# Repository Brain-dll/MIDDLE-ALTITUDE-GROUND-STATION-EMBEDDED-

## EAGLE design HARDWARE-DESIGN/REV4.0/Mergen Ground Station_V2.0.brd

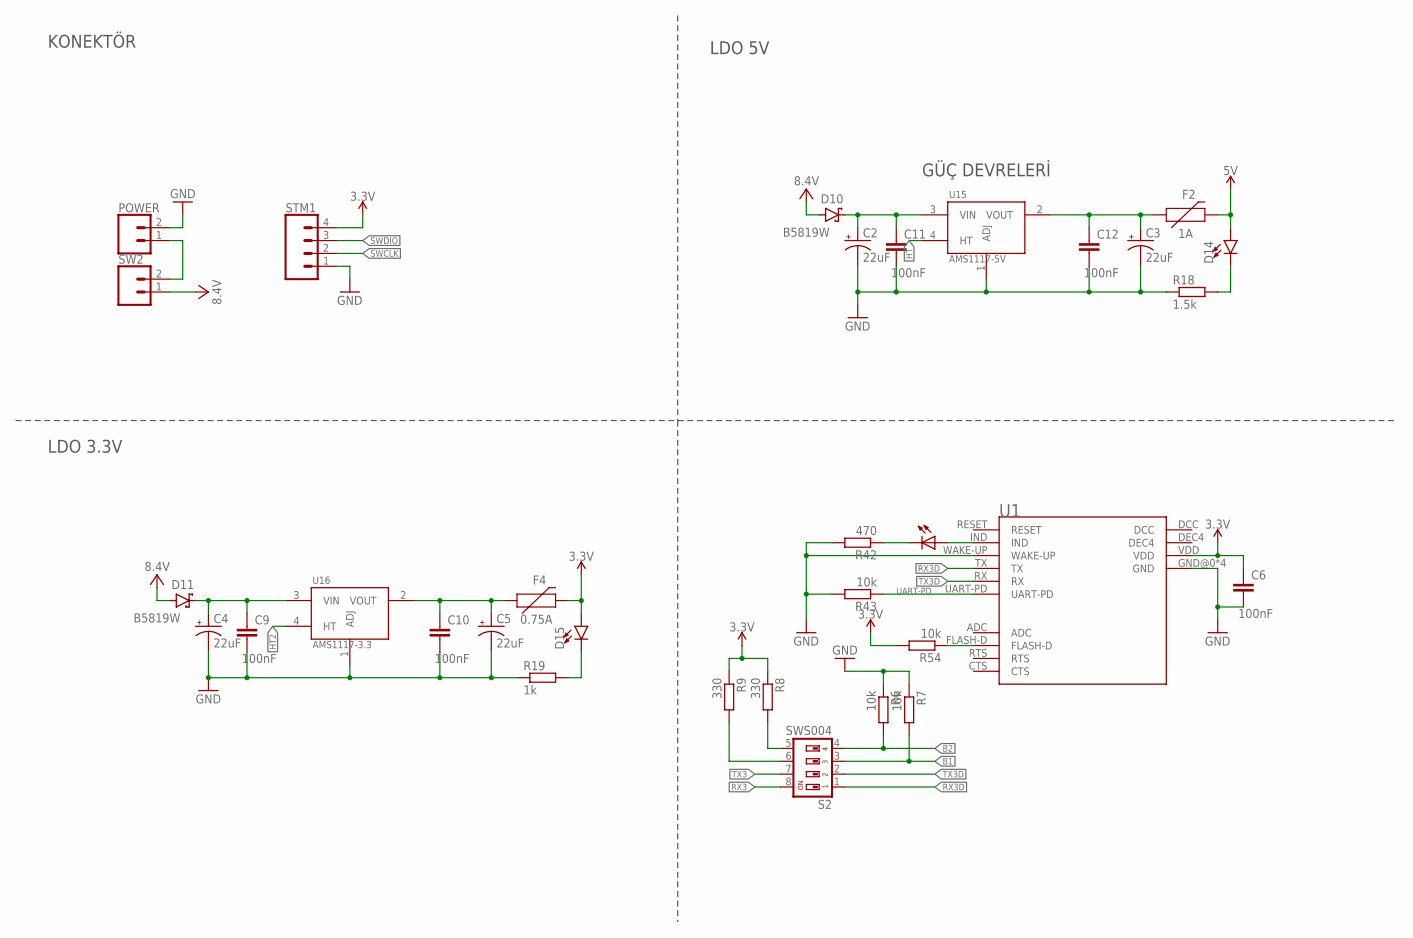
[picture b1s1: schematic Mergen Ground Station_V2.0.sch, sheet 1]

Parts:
C2, C3, C4, C5: 22uF; CT3528
C6, C9, C10, C11, C12: 100nF; C0603
D10, D11: B5819W; SODFL3718X115
D14, D15: LED0603; LED-0603
DRM3: kirmizi; CHIP-LED0805
F2: 1A; 1206
F4: 0.75A; 1206
POWER: CONN_023.5MM-NO_SILK; SCREWTERMINAL-3.5MM-2-NS
R6, R7, R43, R54: 10k; R0603
R8, R9: 330; R0603
R18: 1.5k; R0603
R19: 1k; R0603
R42: 470; R0603
S2: SWS004; SMS-004
STM1: CONN_04; 1X04
SW2: CONN_023.5MM-NO_SILK; SCREWTERMINAL-3.5MM-2-NS
U1: MDBT42T-AT
U15: AMS1117-5V; SOT229P700X180-4N
U16: AMS1117-3.3; SOT229P700X180-4N

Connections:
3.3V: C6.1, D15.A, F4.2, R8.1, R9.1, R54.2, STM1.4, U1.VDD; also elsewhere on the board
5V: D14.A, F2.2; also elsewhere on the board
B1: R7.2, S2.3; also elsewhere on the board
B2: R6.2, S2.4; also elsewhere on the board
FLASH-D: R54.1, U1.FLASH-D; also elsewhere on the board
GND: C2.-, C3.-, C4.-, C5.-, C6.2, C9.2, C10.2, C11.2, C12.2, POWER.2, R6.1, R7.1, R18.1, R19.1, R42.2, R43.2, STM1.1, U1.GND@0 (GND), U1.GND@1 (GND), U1.GND@2 (GND), U1.GND@3 (GND), U1.WAKE-UP, U15.1 (ADJ), U16.1 (ADJ); also elsewhere on the board
HT: U15.4 (HT)
HT2: U16.4 (HT)
unnamed: DRM3.A, U1.IND
unnamed: DRM3.C, R42.1
unnamed: R9.2, S2.6
unnamed: R8.2, S2.5
unnamed: C2.+, C11.1, D10.1 (C), U15.3 (VIN)
unnamed: C3.+, C12.1, F2.1, U15.2 (VOUT)
unnamed: C4.+, C9.1, D11.1 (C), U16.3 (VIN)
unnamed: C5.+, C10.1, F4.1, U16.2 (VOUT)
unnamed: POWER.1, SW2.2
unnamed: D14.C, R18.2
unnamed: D15.C, R19.2
RX3: S2.8; also elsewhere on the board
RX3D: S2.1, U1.TX
SWCLK: STM1.2; also elsewhere on the board
SWDIO: STM1.3; also elsewhere on the board
TX3: S2.7; also elsewhere on the board
TX3D: S2.2, U1.RX
UART-PD: R43.1, U1.UART-PD; also elsewhere on the board
VCC: D10.2 (A), D11.2 (A), SW2.1; also elsewhere on the board

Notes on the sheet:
GÜÇ DEVRELERİ
KONEKTÖR
LDO 5V
LDO 3.3V

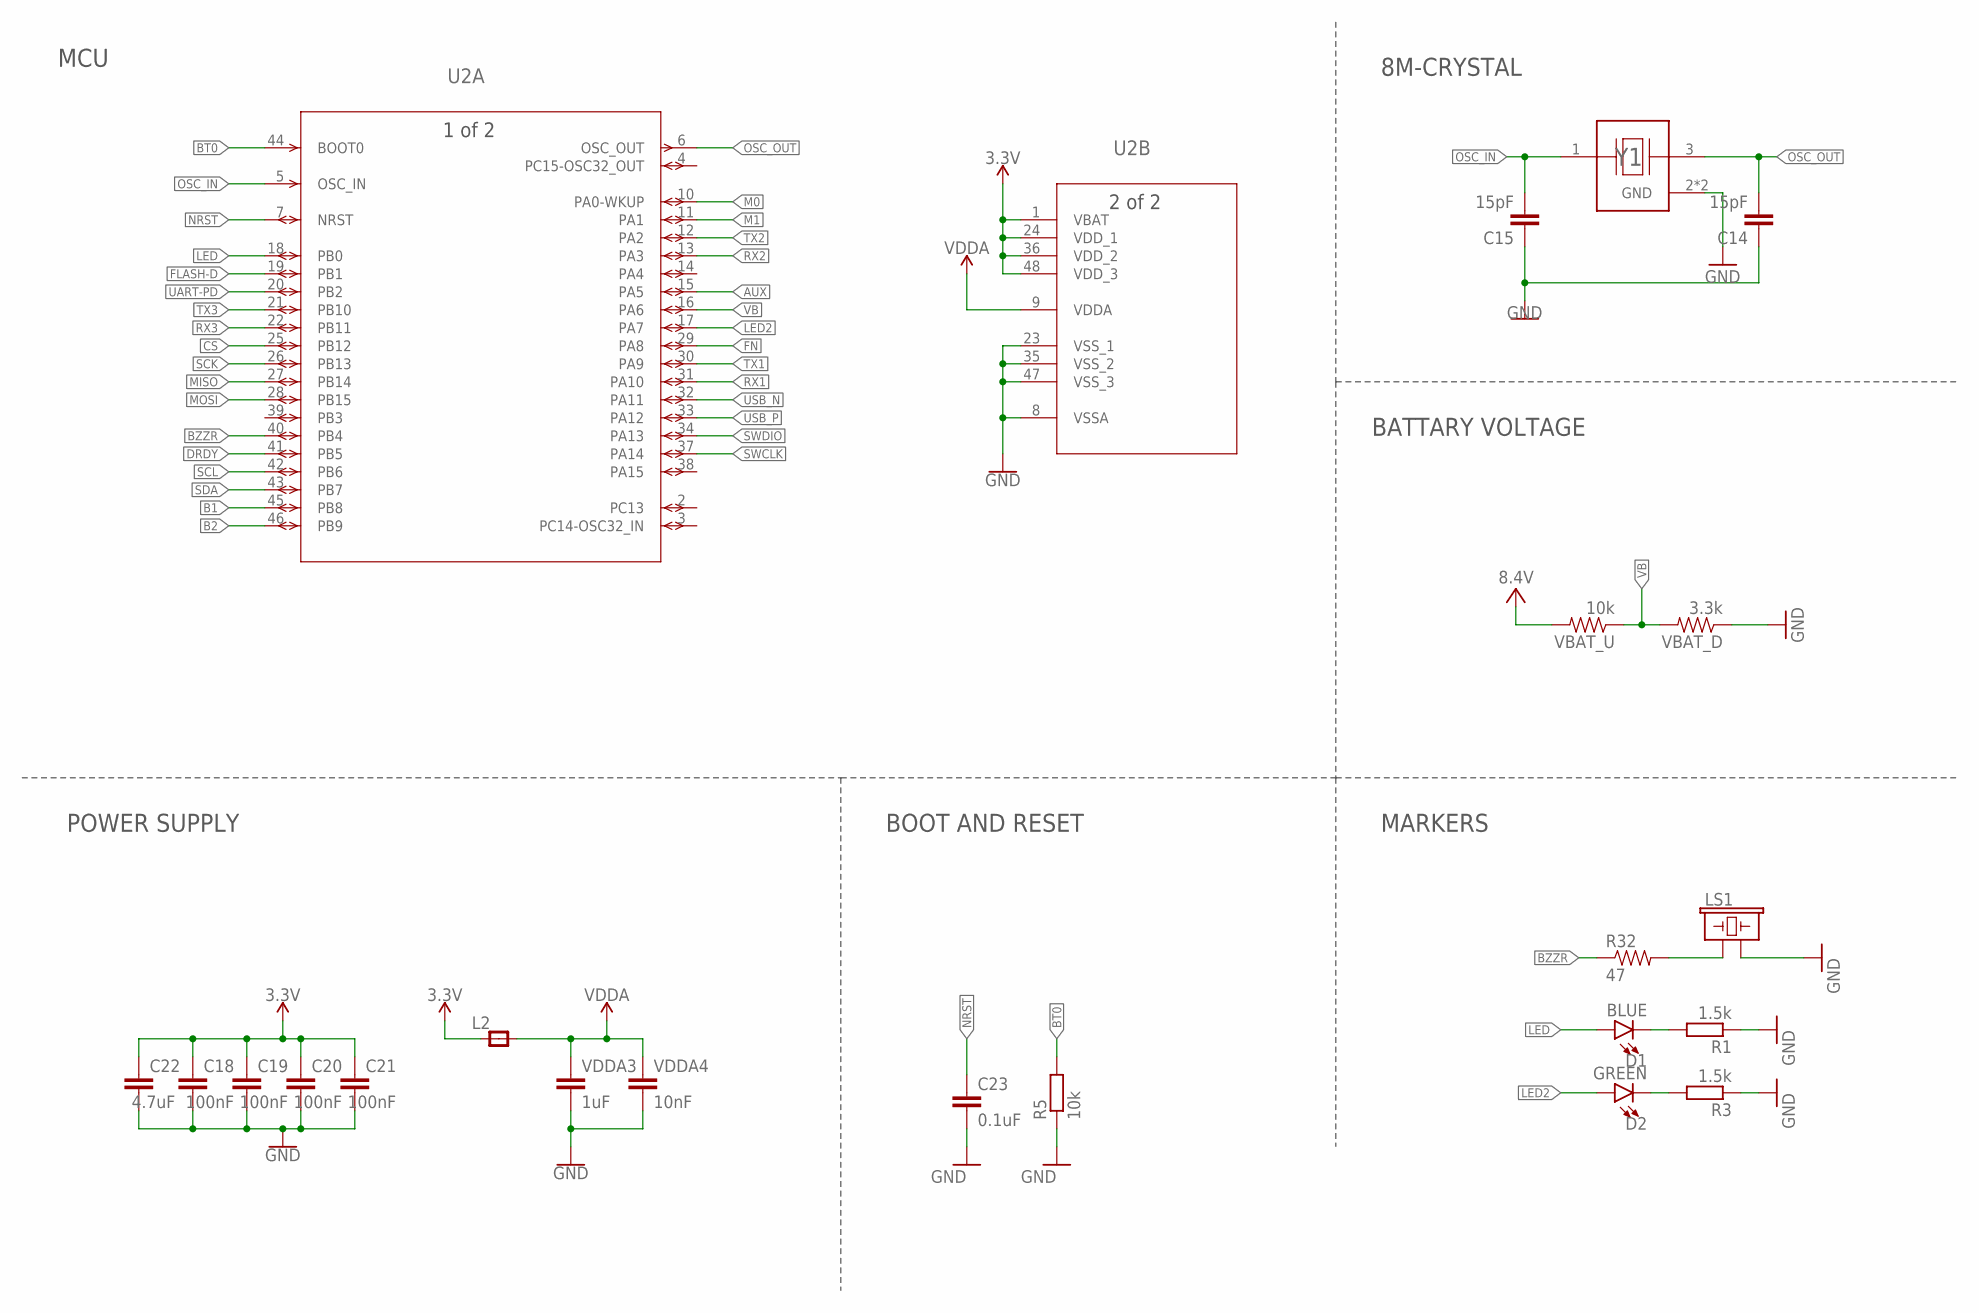
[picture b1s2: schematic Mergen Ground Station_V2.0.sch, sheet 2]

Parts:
C14, C15: 15pF; C0603
C18, C19, C20, C21: 100nF; C0603
C22: 4.7uF; C0603
C23: 0.1uF; C0603
D1: BLUE; LED-0603
D2: GREEN; LED-0603
L2: RC-MASTER-SMD_FB_0805MP; RC-MASTER-SMD_L0805MP
LS1: BUZZER-PTH; BUZZER-12MM
R1, R3: 1.5k; R0603
R5: 10k; R0603
R32: 47; 0603
U2: STM32F103C8T6; LQFP48-7X7MM
VBAT_D: 3.3k; 0603-RES
VBAT_U: 10k; 0603-RES
VDDA3: 1uF; 0603
VDDA4: 10nF; 0603
Y1: ABMM2-8.000MHZ-E2-T; XTAL_ABMM2-8.000MHZ-E2-T

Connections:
3.3V: C18.1, C19.1, C20.1, C21.1, C22.1, L2.1, U2.1 (VBAT), U2.24 (VDD_1), U2.36 (VDD_2), U2.48 (VDD_3); also elsewhere on the board
AUX: U2.15 (PA5); also elsewhere on the board
B1: U2.45 (PB8); also elsewhere on the board
B2: U2.46 (PB9); also elsewhere on the board
BT0: R5.2, U2.44 (BOOT0)
BZZR: R32.1, U2.40 (PB4)
CS: U2.25 (PB12); also elsewhere on the board
DRDY: U2.41 (PB5); also elsewhere on the board
FLASH-D: U2.19 (PB1); also elsewhere on the board
FN: U2.29 (PA8); also elsewhere on the board
GND: C14.1, C15.1, C18.2, C19.2, C20.2, C21.2, C22.2, C23.2, LS1.- (2), R1.1, R3.1, R5.1, U2.8 (VSSA), U2.23 (VSS_1), U2.35 (VSS_2), U2.47 (VSS_3), VBAT_D.1, VDDA3.2, VDDA4.2, Y1.2 (GND), Y1.4 (GND); also elsewhere on the board
LED: D1.A, U2.18 (PB0)
LED2: D2.A, U2.17 (PA7)
M0: U2.10 (PA0-WKUP); also elsewhere on the board
M1: U2.11 (PA1); also elsewhere on the board
MISO: U2.27 (PB14); also elsewhere on the board
MOSI: U2.28 (PB15); also elsewhere on the board
unnamed: D1.C, R1.2
unnamed: D2.C, R3.2
unnamed: LS1.+ (1), R32.2
NRST: C23.1, U2.7 (NRST)
OSC_IN: C15.2, U2.5 (OSC_IN), Y1.1
OSC_OUT: C14.2, U2.6 (OSC_OUT), Y1.3
RX1: U2.31 (PA10); also elsewhere on the board
RX2: U2.13 (PA3); also elsewhere on the board
RX3: U2.22 (PB11); also elsewhere on the board
SCK: U2.26 (PB13); also elsewhere on the board
SCL: U2.42 (PB6); also elsewhere on the board
SDA: U2.43 (PB7); also elsewhere on the board
SWCLK: U2.37 (PA14); also elsewhere on the board
SWDIO: U2.34 (PA13); also elsewhere on the board
TX1: U2.30 (PA9); also elsewhere on the board
TX2: U2.12 (PA2); also elsewhere on the board
TX3: U2.21 (PB10); also elsewhere on the board
UART-PD: U2.20 (PB2); also elsewhere on the board
USB_N: U2.32 (PA11); also elsewhere on the board
USB_P: U2.33 (PA12); also elsewhere on the board
VB: U2.16 (PA6), VBAT_D.2, VBAT_U.1
VCC: VBAT_U.2; also elsewhere on the board
VDDA: L2.2, U2.9 (VDDA), VDDA3.1, VDDA4.1

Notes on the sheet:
MCU
8M-CRYSTAL
BATTARY VOLTAGE
MARKERS
BOOT AND RESET
POWER SUPPLY

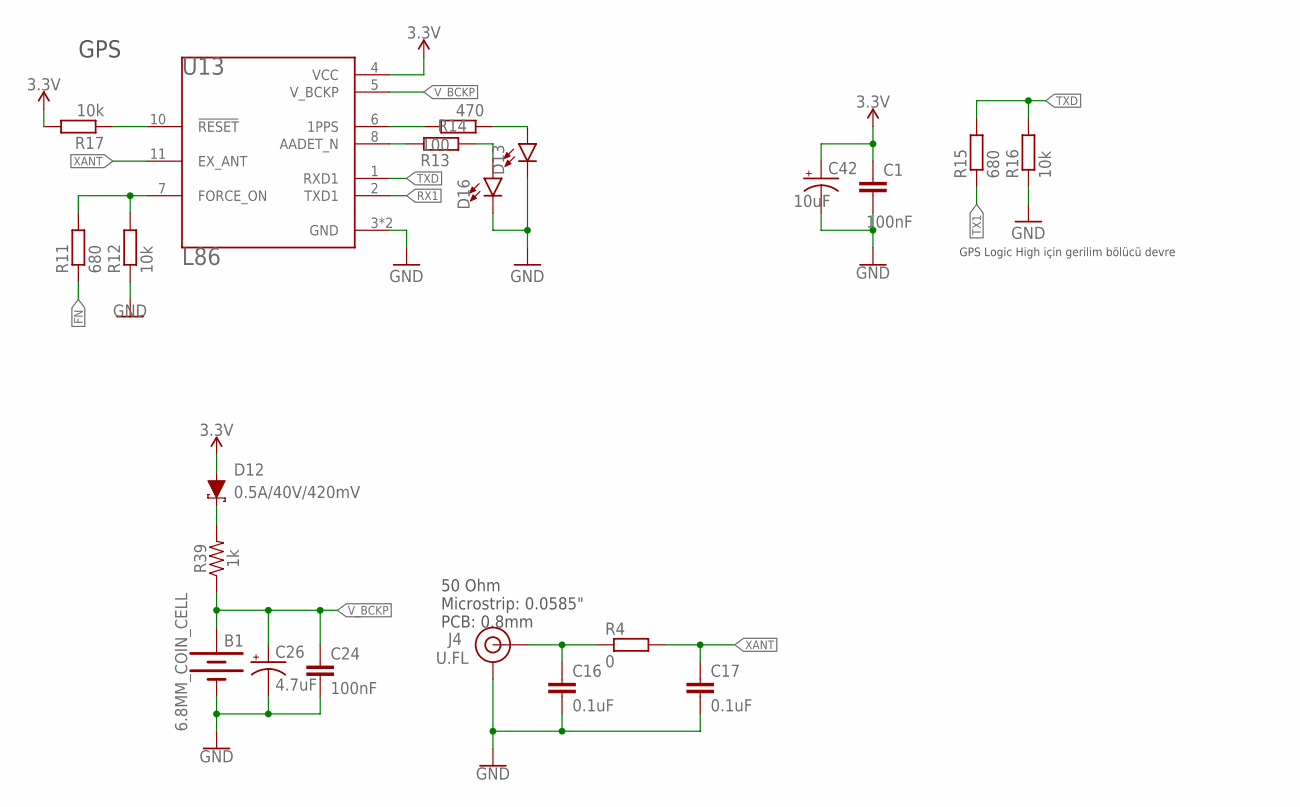
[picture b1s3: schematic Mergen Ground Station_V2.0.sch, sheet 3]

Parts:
B1: 6.8MM_COIN_CELL; BATTCON-6.8MM
C1, C24: 100nF; C0603
C16, C17: 0.1uF; C0603
C26: 4.7uF; A/3216-18R
C42: 10uF; EIA3216
D12: 0.5A/40V/420mV; SOD-323
D13, D16: LED0603; LED-0603
J4: U.FL
R4: 0; R0603
R11, R15: 680; R0603
R12, R16, R17: 10k; R0603
R13: 100; R0603
R14: 470; R0603
R39: 1k; 0603
U13: L86; XCVR_L86

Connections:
3.3V: C1.1, C42.+, D12.A, R17.2, U13.4 (VCC); also elsewhere on the board
FN: R11.1; also elsewhere on the board
GND: B1.-, C1.2, C16.2, C17.2, C24.2, C26.-, C42.-, D13.C, D16.C, J4.1 (GND), J4.2 (GND), R12.1, R16.1, U13.3 (GND), U13.12 (GND); also elsewhere on the board
unnamed: D16.A, R13.1
unnamed: D12.C, R39.2
unnamed: R17.1, U13.10 (!RESET)
unnamed: R14.2, U13.6 (1PPS)
unnamed: D13.A, R14.1
unnamed: R13.2, U13.8 (AADET_N)
unnamed: C16.1, J4.FEED (SIGNAL), R4.1
unnamed: R11.2, R12.2, U13.7 (FORCE_ON)
RX1: U13.2 (TXD1); also elsewhere on the board
TX1: R15.1; also elsewhere on the board
TXD: R15.2, R16.2, U13.1 (RXD1)
V_BCKP: B1.+, C24.1, C26.+, R39.1, U13.5 (V_BCKP)
XANT: C17.1, R4.2, U13.11 (EX_ANT)

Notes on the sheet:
GPS
GPS Logic High için gerilim bölücü devre
50 Ohm Microstrip: 0.0585" PCB: 0.8mm

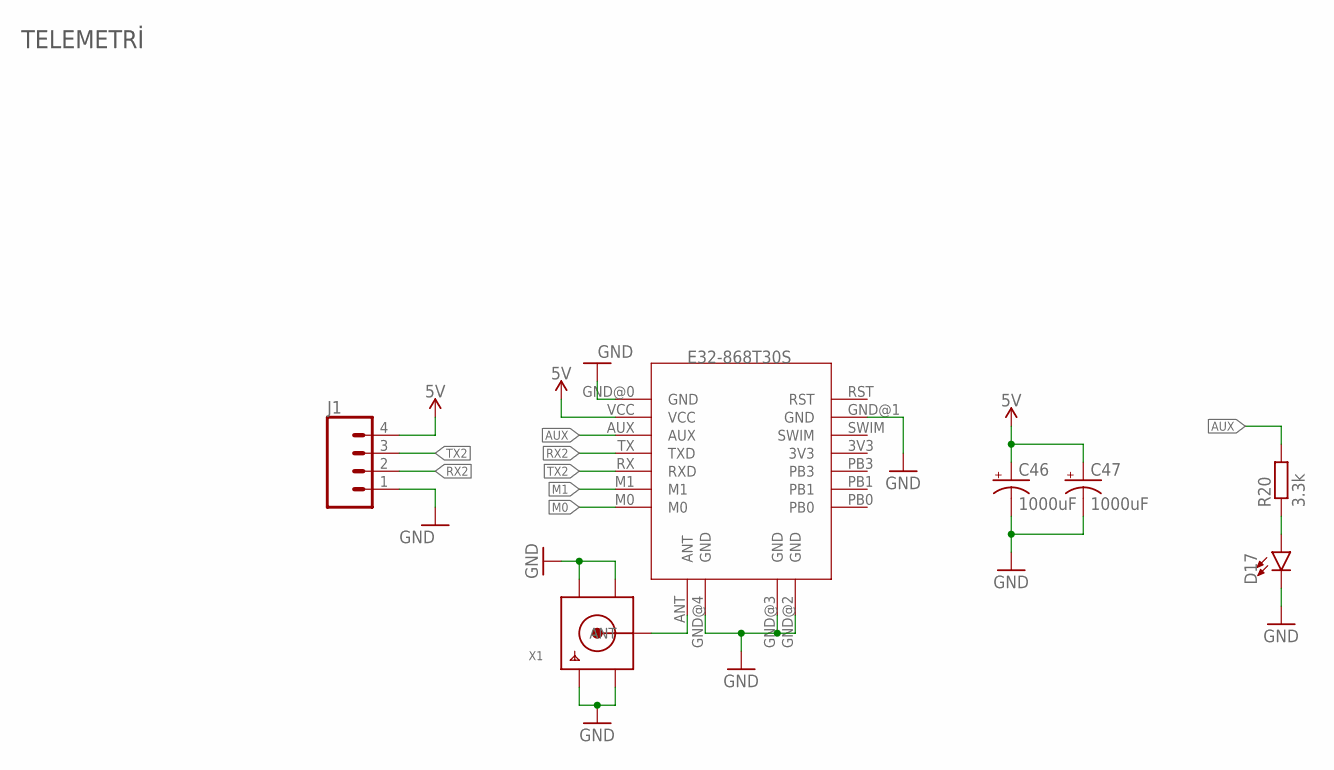
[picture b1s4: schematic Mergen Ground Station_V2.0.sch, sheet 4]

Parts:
C46, C47: 1000uF; 150CLZ-1010
D17: LED0603; LED-0603
J1: CONN_04; 1X04
R20: 3.3k; R0603
U14: E32-868T30S
X1: SMACONNECTOR; SMA90_DIP

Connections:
5V: C46.+, C47.+, J1.4, U14.VCC; also elsewhere on the board
AUX: R20.2, U14.AUX; also elsewhere on the board
GND: C46.-, C47.-, D17.C, J1.1, U14.GND@0 (GND), U14.GND@1 (GND), U14.GND@2 (GND), U14.GND@3 (GND), U14.GND@4 (GND), X1.GND1, X1.GND2, X1.GND3, X1.GND4; also elsewhere on the board
M0: U14.M0; also elsewhere on the board
M1: U14.M1; also elsewhere on the board
unnamed: U14.ANT, X1.ANTENNA (ANT)
unnamed: D17.A, R20.1
RX2: J1.2, U14.TX (TXD); also elsewhere on the board
TX2: J1.3, U14.RX (RXD); also elsewhere on the board

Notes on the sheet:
TELEMETRİ

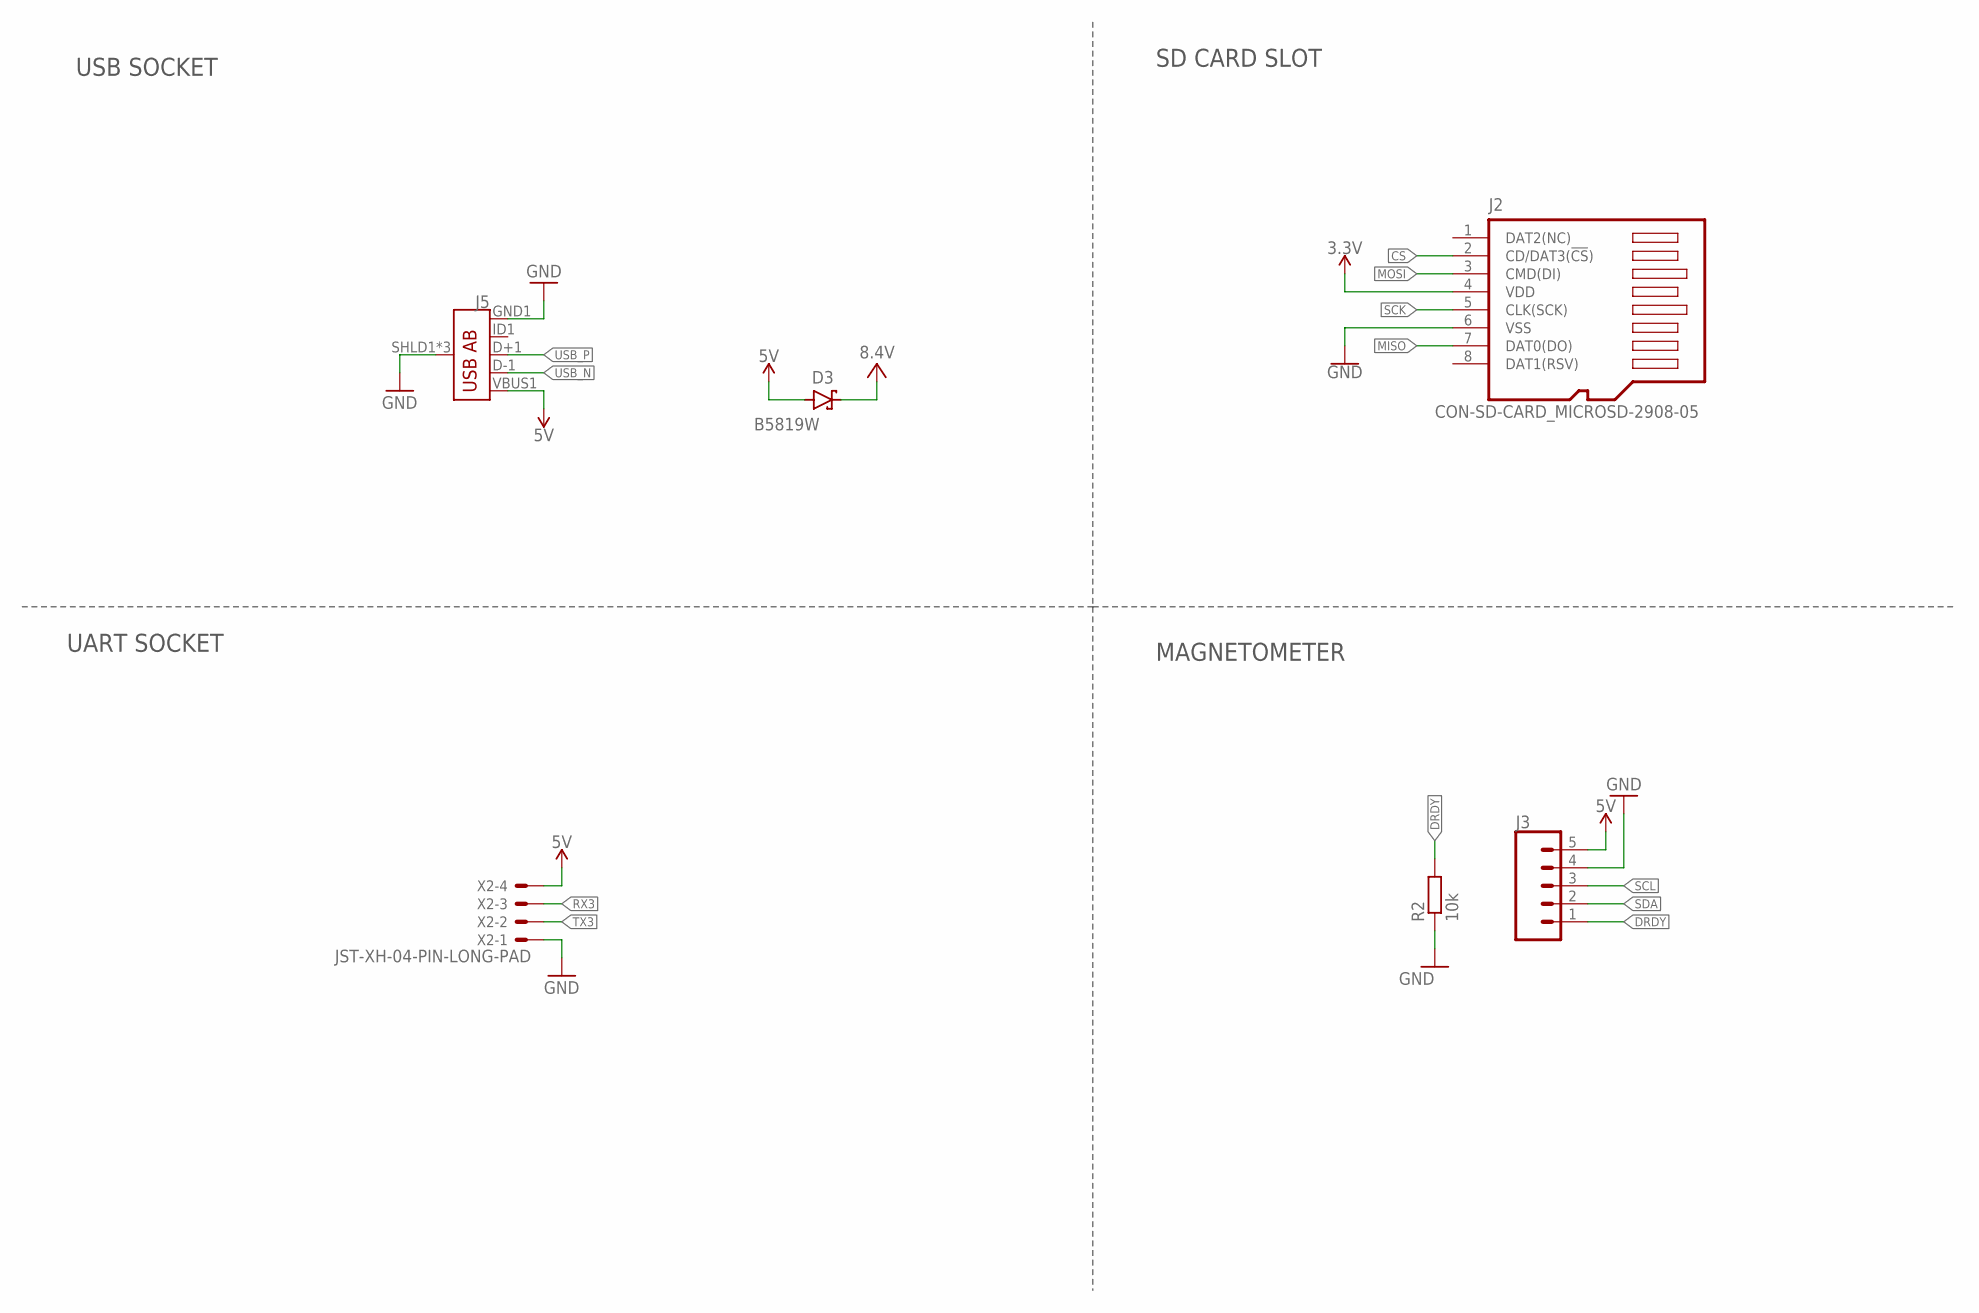
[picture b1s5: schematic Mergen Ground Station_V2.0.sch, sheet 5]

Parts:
D3: B5819W; SODFL3718X115
J2: CON-SD-CARD_MICROSD-2908-05; CON-SD-CARD_2908-05
J3: CONN_05LOCK_LONGPADS; 1X05_LOCK_LONGPADS
J5: USB_AB_SMT; USB-AB-MICRO-SMD
R2: 10k; R0603
X2: JST-XH-04-PIN-LONG-PAD; JST-XH-04-PACKAGE-LONG-PAD

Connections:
3.3V: J2.4 (VDD); also elsewhere on the board
5V: D3.2 (A), J3.5, J5.VBUS1 (VBUS), X2.4; also elsewhere on the board
CS: J2.2 (CD/DAT3(!CS!)); also elsewhere on the board
DRDY: J3.1, R2.2; also elsewhere on the board
GND: J2.6 (VSS), J3.4, J5.GND1 (GND), J5.SHLD1 (SHIELD), J5.SHLD2 (SHIELD), J5.SHLD3 (SHIELD), R2.1, X2.1; also elsewhere on the board
MISO: J2.7 (DAT0(DO)); also elsewhere on the board
MOSI: J2.3 (CMD(DI)); also elsewhere on the board
RX3: X2.3; also elsewhere on the board
SCK: J2.5 (CLK(SCK)); also elsewhere on the board
SCL: J3.3; also elsewhere on the board
SDA: J3.2; also elsewhere on the board
TX3: X2.2; also elsewhere on the board
USB_N: J5.D-1 (D-); also elsewhere on the board
USB_P: J5.D+1 (D+); also elsewhere on the board
VCC: D3.1 (C); also elsewhere on the board

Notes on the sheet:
USB SOCKET
SD CARD SLOT
UART SOCKET
MAGNETOMETER

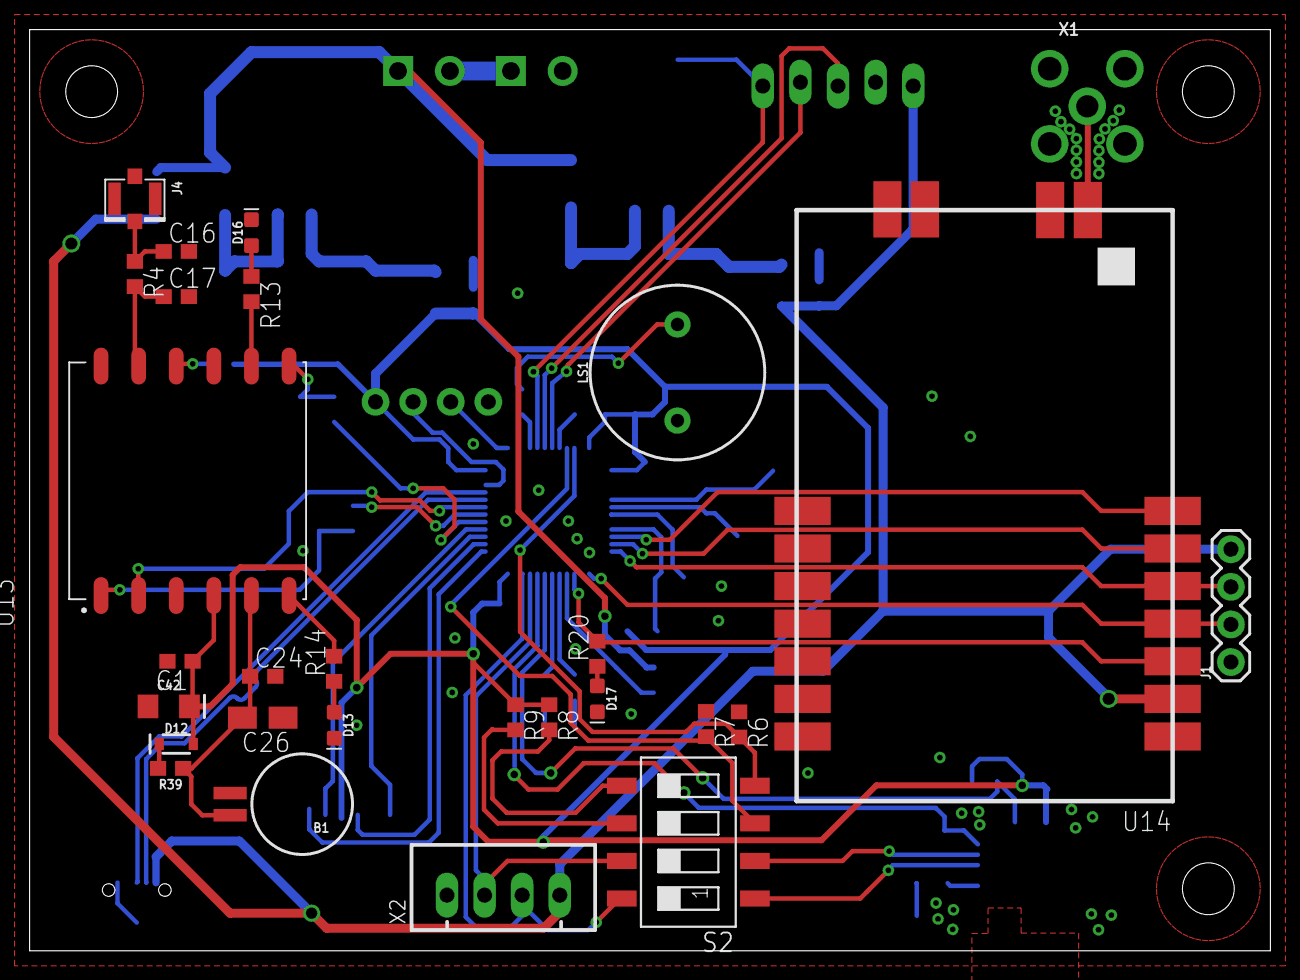
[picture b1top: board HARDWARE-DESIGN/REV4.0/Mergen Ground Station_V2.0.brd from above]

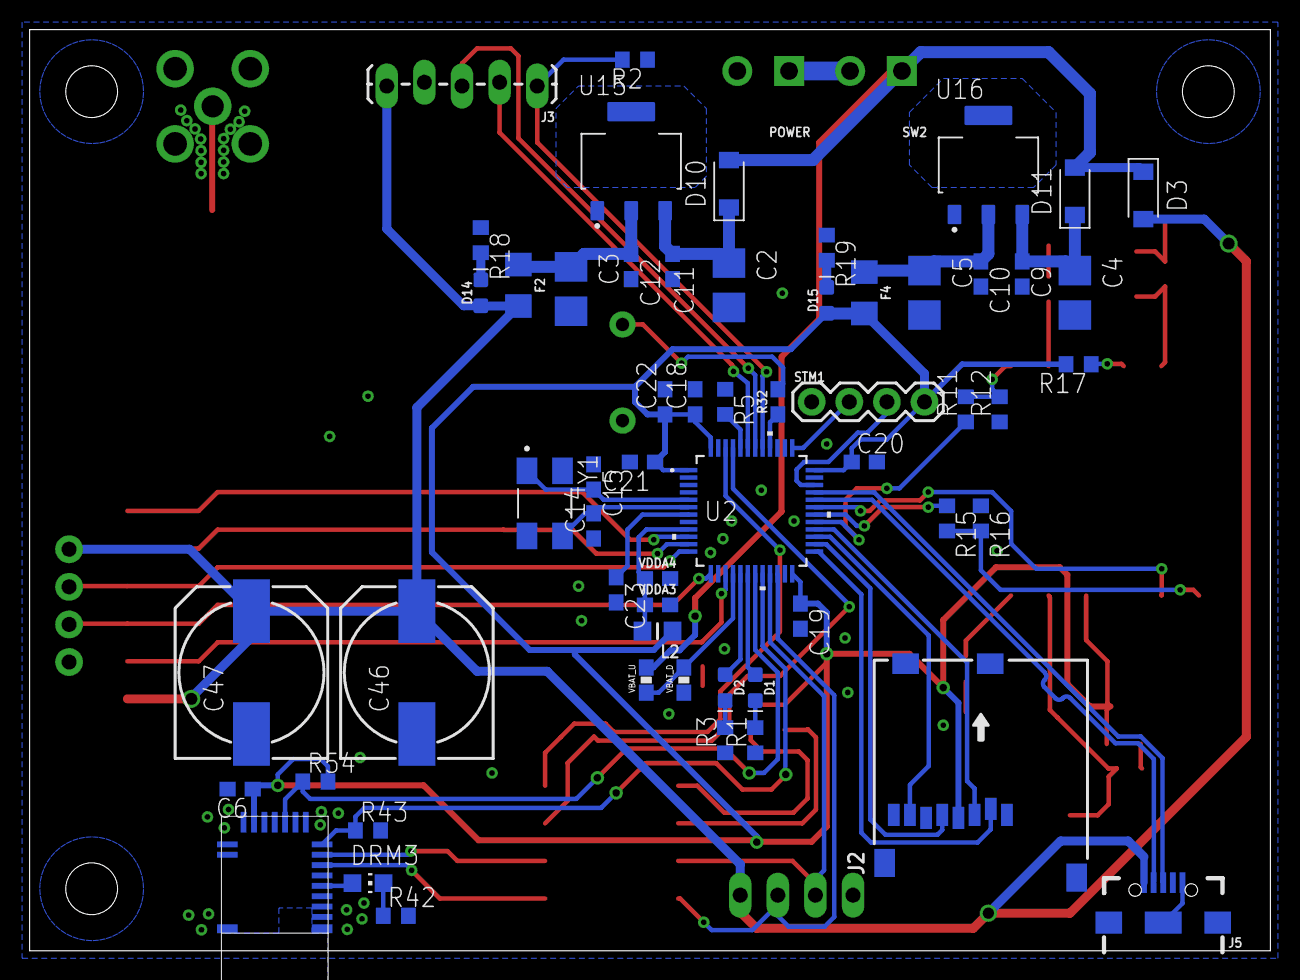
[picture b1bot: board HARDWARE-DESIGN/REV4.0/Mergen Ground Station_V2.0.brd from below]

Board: 2 copper layers, 83.8 x 62.2 mm, 88 parts (60 on the bottom side), 67 nets.

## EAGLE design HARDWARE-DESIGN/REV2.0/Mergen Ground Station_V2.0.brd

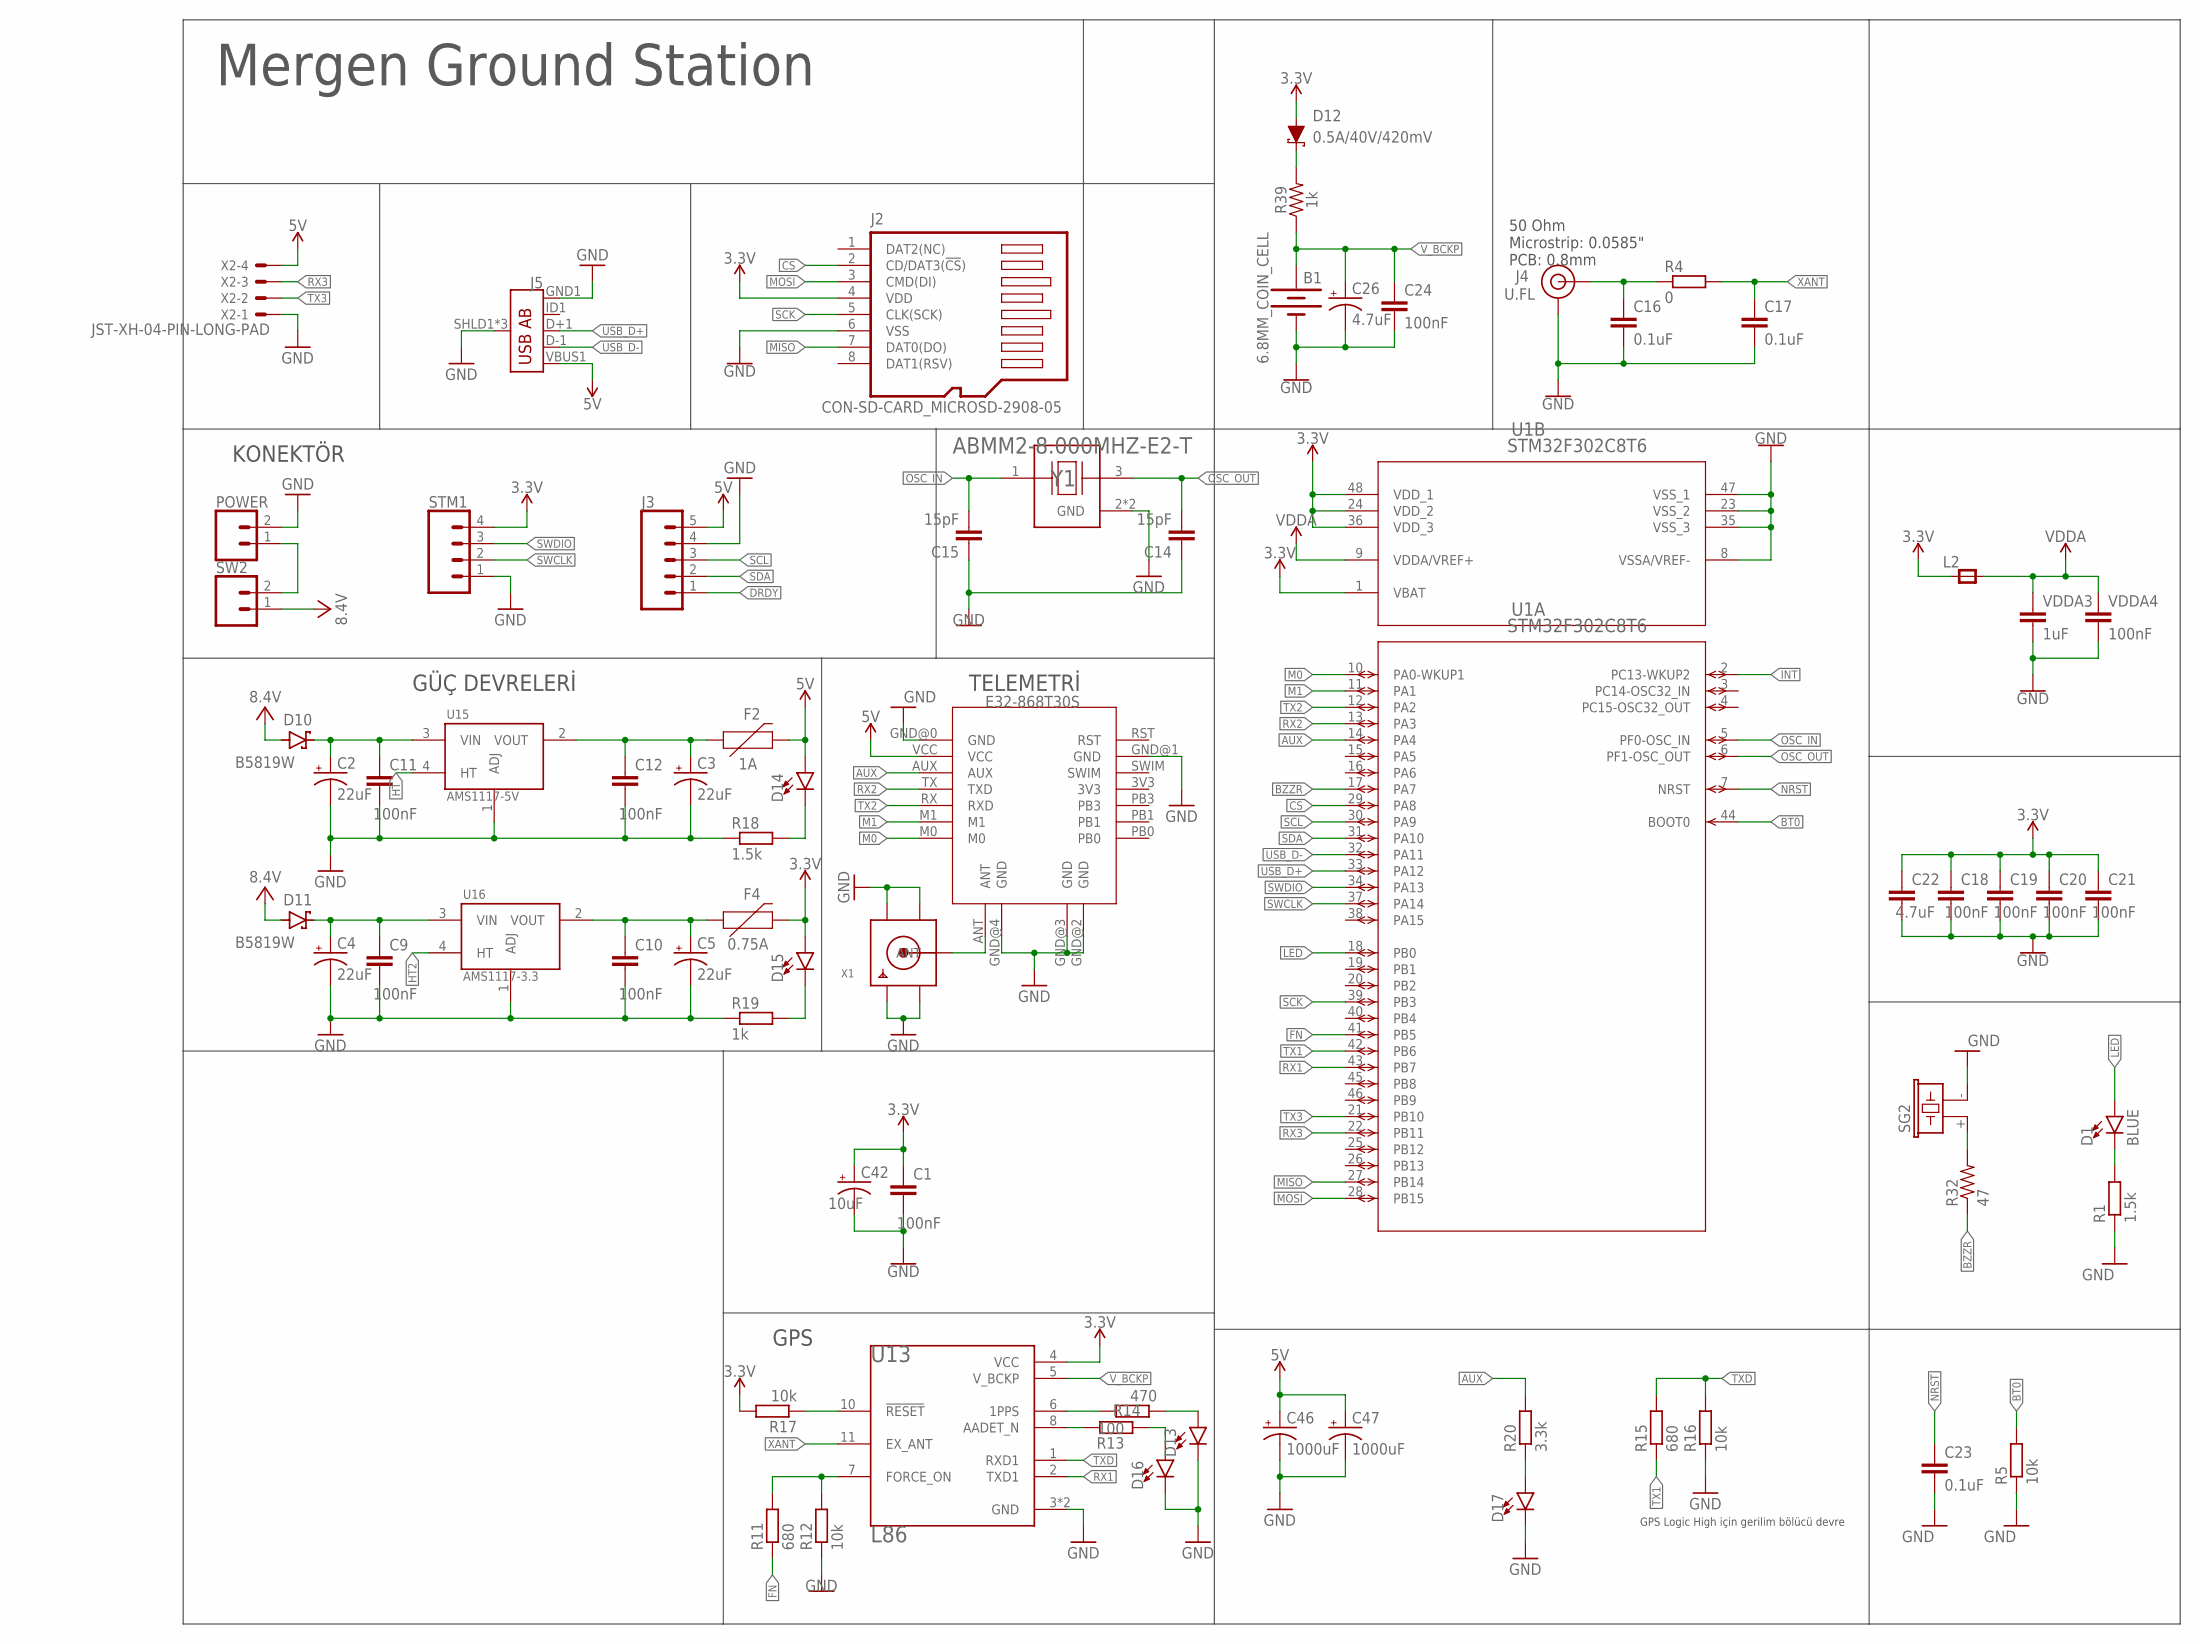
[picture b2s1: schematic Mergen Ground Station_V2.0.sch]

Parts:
B1: 6.8MM_COIN_CELL; BATTCON-6.8MM
C1, C9, C10, C11, C12, C18, C19, C20, C21, C24: 100nF; C0603
C2, C3, C4, C5: 22uF; CT3528
C14, C15: 15pF; C0603
C16, C17, C23: 0.1uF; C0603
C22: 4.7uF; C0603
C26: 4.7uF; A/3216-18R
C42: 10uF; EIA3216
C46, C47: 1000uF; 150CLZ-1010
D1: BLUE; LED-0603
D10, D11: B5819W; SODFL3718X115
D12: 0.5A/40V/420mV; SOD-323
D13, D14, D15, D16, D17: LED0603; LED-0603
F2: 1A; 1206
F4: 0.75A; 1206
J2: CON-SD-CARD_MICROSD-2908-05; CON-SD-CARD_2908-05
J3: CONN_05LOCK_LONGPADS; 1X05_LOCK_LONGPADS
J4: U.FL
J5: USB_AB_SMT; USB-AB-MICRO-SMD
L2: RC-MASTER-SMD_FB_0805MP; RC-MASTER-SMD_L0805MP
POWER: CONN_023.5MM-NO_SILK; SCREWTERMINAL-3.5MM-2-NS
R1, R18: 1.5k; R0603
R4: 0; R0603
R5, R12, R16, R17: 10k; R0603
R11, R15: 680; R0603
R13: 100; R0603
R14: 470; R0603
R19: 1k; R0603
R20: 3.3k; R0603
R32: 47; 0603
R39: 1k; 0603
SG2: F/CM12P
STM1: CONN_04; 1X04
SW2: CONN_023.5MM-NO_SILK; SCREWTERMINAL-3.5MM-2-NS
U1: STM32F302C8T6; LQFP48-7X7MM
U13: L86; XCVR_L86
U14: E32-868T30S
U15: AMS1117-5V; SOT229P700X180-4N
U16: AMS1117-3.3; SOT229P700X180-4N
VDDA3: 1uF; 0603
VDDA4: 100nF; 0603
X1: SMACONNECTOR; SMA90_DIP
X2: JST-XH-04-PIN-LONG-PAD; JST-XH-04-PACKAGE-LONG-PAD
Y1: ABMM2-8.000MHZ-E2-T; XTAL_ABMM2-8.000MHZ-E2-T

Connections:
3.3V: C1.1, C18.1, C19.1, C20.1, C21.1, C22.1, C42.+, D12.A, D15.A, F4.2, J2.4 (VDD), L2.1, R17.2, STM1.4, U1.1 (VBAT), U1.24 (VDD_2), U1.36 (VDD_3), U1.48 (VDD_1), U13.4 (VCC)
5V: C46.+, C47.+, D14.A, F2.2, J3.5, J5.VBUS1 (VBUS), U14.VCC, X2.4
AUX: R20.2, U1.14 (PA4), U14.AUX
BT0: R5.2, U1.44 (BOOT0)
BZZR: R32.1, U1.17 (PA7)
CS: J2.2 (CD/DAT3(!CS!)), U1.29 (PA8)
DRDY: J3.1
FN: R11.1, U1.41 (PB5)
GND: B1.-, C1.2, C2.-, C3.-, C4.-, C5.-, C9.2, C10.2, C11.2, C12.2, C14.1, C15.1, C16.2, C17.2, C18.2, C19.2, C20.2, C21.2, C22.2, C23.2, C24.2, C26.-, C42.-, C46.-, C47.-, D13.C, D16.C, D17.C, J2.6 (VSS), J3.4, J4.1 (GND), J4.2 (GND), J5.GND1 (GND), J5.SHLD1 (SHIELD), J5.SHLD2 (SHIELD), J5.SHLD3 (SHIELD), POWER.2, R1.1, R5.1, R12.1, R16.1, R18.1, R19.1, SG2.- (2), STM1.1, U1.8 (VSSA/VREF-), U1.23 (VSS_2), U1.35 (VSS_3), U1.47 (VSS_1), U13.3 (GND), U13.12 (GND), U14.GND@0 (GND), U14.GND@1 (GND), U14.GND@2 (GND), U14.GND@3 (GND), U14.GND@4 (GND), U15.1 (ADJ), U16.1 (ADJ), VDDA3.2, VDDA4.2, X1.GND1, X1.GND2, X1.GND3, X1.GND4, X2.1, Y1.2 (GND), Y1.4 (GND)
HT: U15.4 (HT)
HT2: U16.4 (HT)
INT: U1.2 (PC13-WKUP2)
LED: D1.A, U1.18 (PB0)
M0: U1.10 (PA0-WKUP1), U14.M0
M1: U1.11 (PA1), U14.M1
MISO: J2.7 (DAT0(DO)), U1.27 (PB14)
MOSI: J2.3 (CMD(DI)), U1.28 (PB15)
unnamed: D1.C, R1.2
unnamed: D16.A, R13.1
unnamed: C2.+, C11.1, D10.1 (C), U15.3 (VIN)
unnamed: C3.+, C12.1, F2.1, U15.2 (VOUT)
unnamed: C4.+, C9.1, D11.1 (C), U16.3 (VIN)
unnamed: C5.+, C10.1, F4.1, U16.2 (VOUT)
unnamed: U14.ANT, X1.ANTENNA (ANT)
unnamed: R32.2, SG2.+ (1)
unnamed: POWER.1, SW2.2
unnamed: D12.C, R39.2
unnamed: R17.1, U13.10 (!RESET)
unnamed: R14.2, U13.6 (1PPS)
unnamed: D13.A, R14.1
unnamed: D14.C, R18.2
unnamed: D15.C, R19.2
unnamed: R13.2, U13.8 (AADET_N)
unnamed: C16.1, J4.FEED (SIGNAL), R4.1
unnamed: R11.2, R12.2, U13.7 (FORCE_ON)
unnamed: D17.A, R20.1
NRST: C23.1, U1.7 (NRST)
OSC_IN: C15.2, U1.5 (PF0-OSC_IN), Y1.1
OSC_OUT: C14.2, U1.6 (PF1-OSC_OUT), Y1.3
RX1: U1.43 (PB7), U13.2 (TXD1)
RX2: U1.13 (PA3), U14.TX (TXD)
RX3: U1.22 (PB11), X2.3
SCK: J2.5 (CLK(SCK)), U1.39 (PB3)
SCL: J3.3, U1.30 (PA9)
SDA: J3.2, U1.31 (PA10)
SWCLK: STM1.2, U1.37 (PA14)
SWDIO: STM1.3, U1.34 (PA13)
TX1: R15.1, U1.42 (PB6)
TX2: U1.12 (PA2), U14.RX (RXD)
TX3: U1.21 (PB10), X2.2
TXD: R15.2, R16.2, U13.1 (RXD1)
USB_D+: J5.D+1 (D+), U1.33 (PA12)
USB_D-: J5.D-1 (D-), U1.32 (PA11)
VCC: D10.2 (A), D11.2 (A), SW2.1
VDDA: L2.2, U1.9 (VDDA/VREF+), VDDA3.1, VDDA4.1
V_BCKP: B1.+, C24.1, C26.+, R39.1, U13.5 (V_BCKP)
XANT: C17.1, R4.2, U13.11 (EX_ANT)

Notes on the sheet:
Mergen Ground Station
GÜÇ DEVRELERİ
TELEMETRİ
GPS
KONEKTÖR
50 Ohm Microstrip: 0.0585" PCB: 0.8mm
GPS Logic High için gerilim bölücü devre

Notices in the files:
parts and their libraries:
SparkFun-Connectors: Licensing: Creative Commons ShareAlike 4.0 International - https://creativecommons.org/licenses/by-sa/4.0
STM32F302C8T6: COPYRIGHT: Copyright (C) 2018 Accelerated Designs. All rights reserved
